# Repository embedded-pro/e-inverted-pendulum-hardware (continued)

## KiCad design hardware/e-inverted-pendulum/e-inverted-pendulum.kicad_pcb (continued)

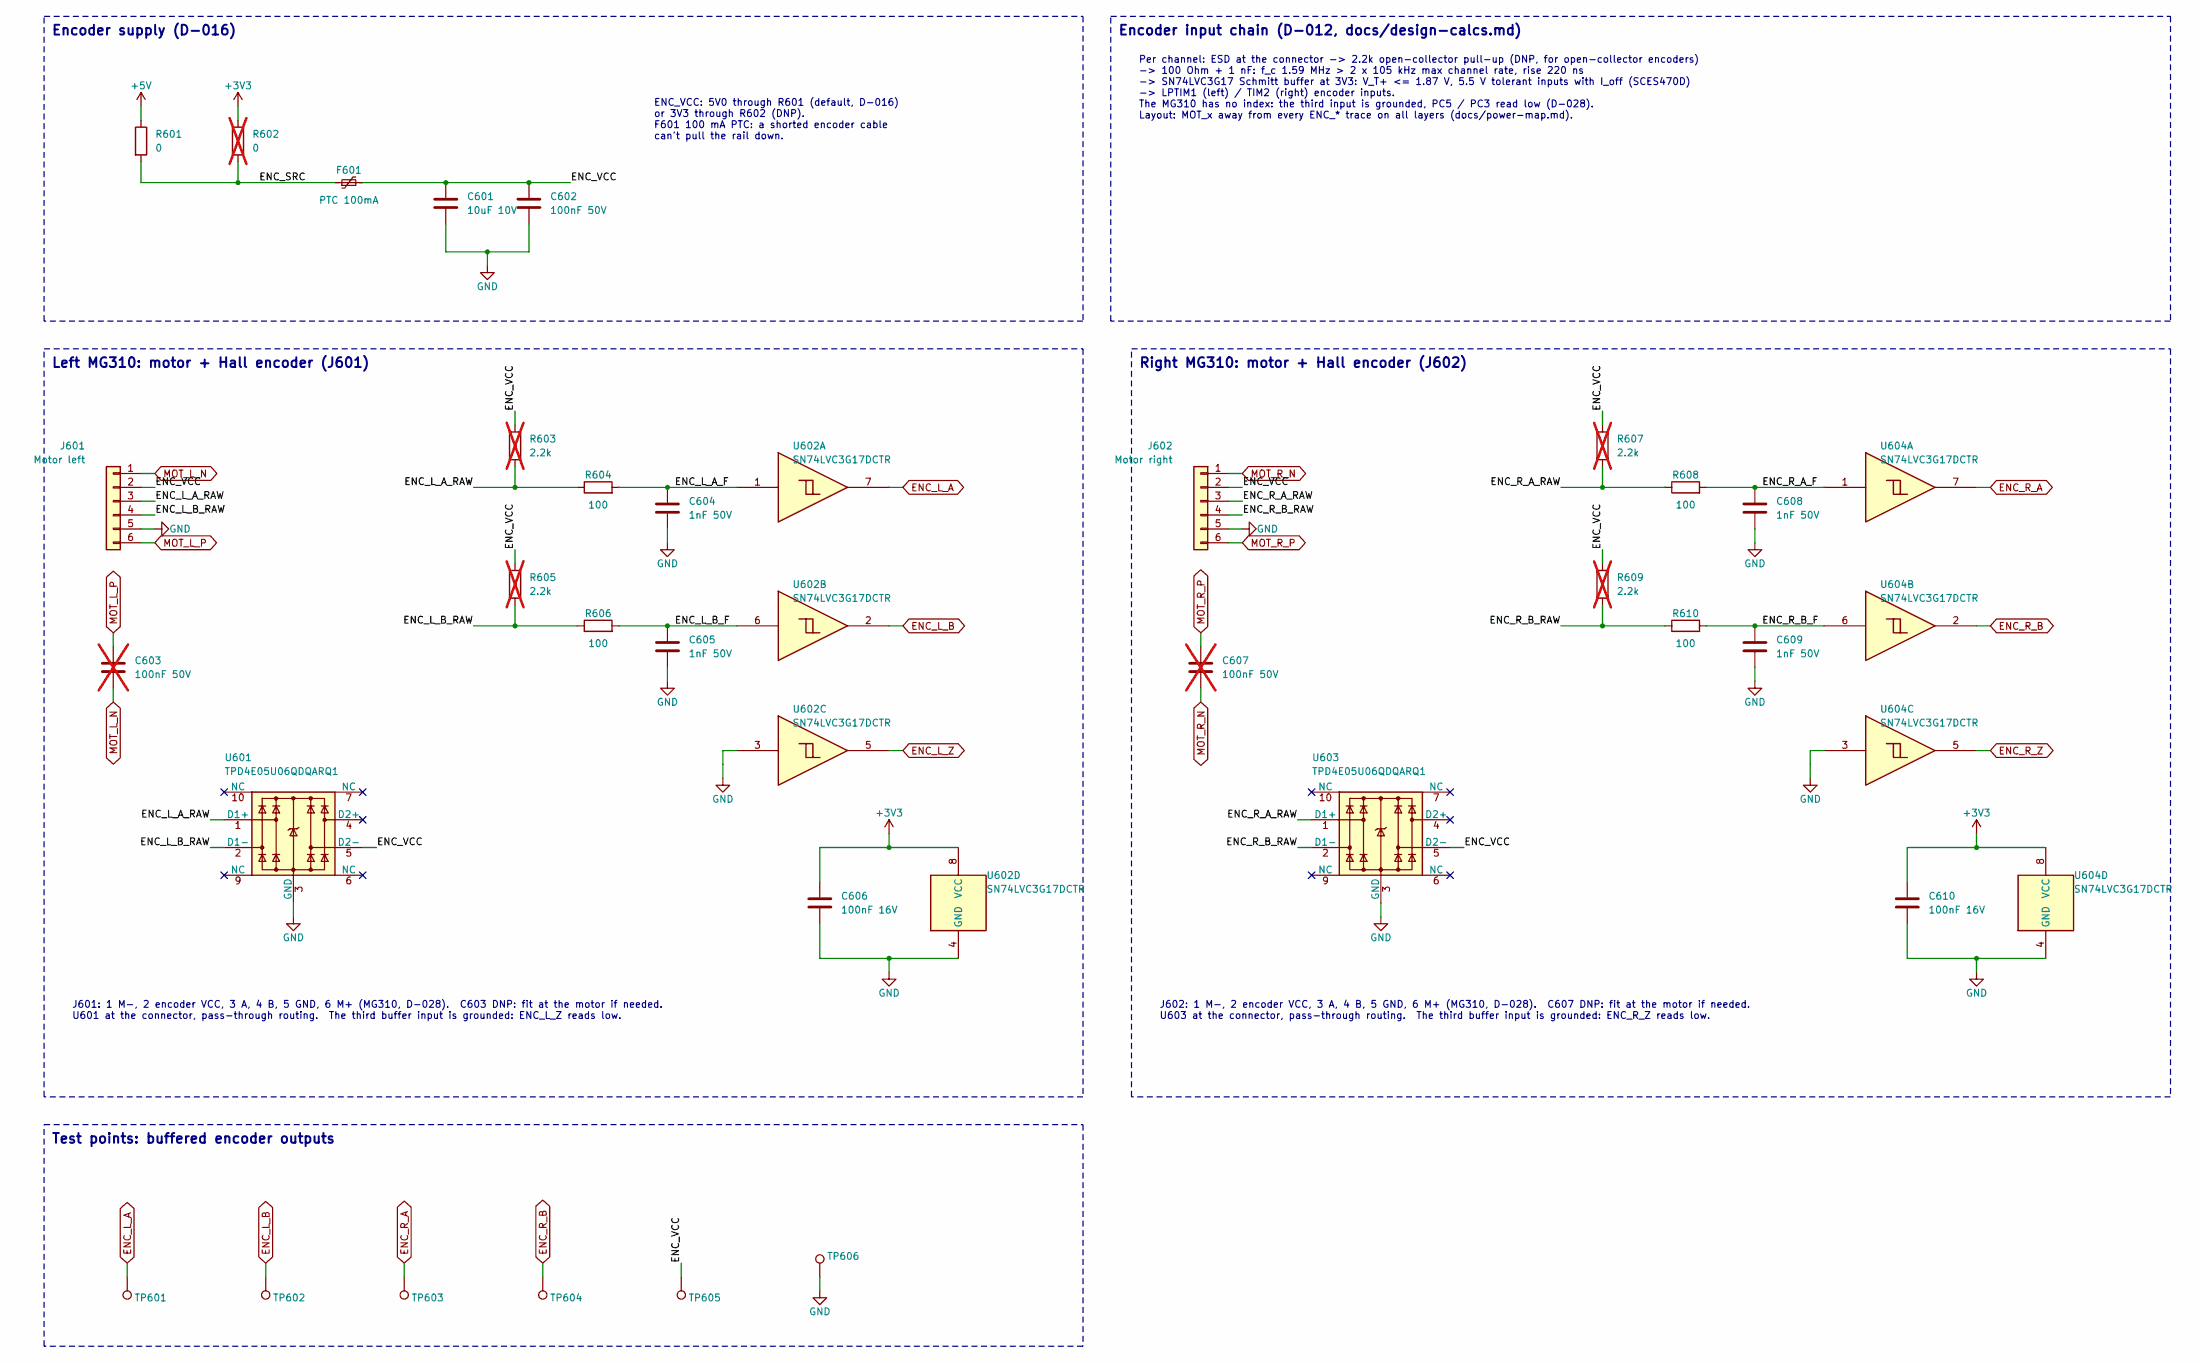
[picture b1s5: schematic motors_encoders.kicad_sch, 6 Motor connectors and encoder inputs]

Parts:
C601: 10uF 10V; C_0603_1608Metric; MPN CL10A106KP8NNNC; LCSC C19702
C602: 100nF 50V; C_0603_1608Metric; MPN CC0603KRX7R9BB104; LCSC C14663
C603, C607: 100nF 50V; C_0603_1608Metric; MPN CC0603KRX7R9BB104; LCSC C14663; not fitted
C604, C605, C608, C609: 1nF 50V; C_0603_1608Metric; MPN CL10B102KB8NNNC; LCSC C1588
C606, C610: 100nF 16V; C_0402_1005Metric; MPN CL05B104KO5NNNC; LCSC C1525
F601: PTC 100mA; Fuse_0805_2012Metric; MPN SMD0805P010TF; LCSC C20975
J601: Motor left; JST_PH_S6B-PH-K_1x06_P2.00mm_Horizontal; MPN S6B-PH-K-S(LF)(SN); LCSC C157920
J602: Motor right; JST_PH_S6B-PH-K_1x06_P2.00mm_Horizontal; MPN S6B-PH-K-S(LF)(SN); LCSC C157920
R601: 0; R_0603_1608Metric; MPN 0603WAF0000T5E; LCSC C21189
R602: 0; R_0603_1608Metric; MPN 0603WAF0000T5E; LCSC C21189; not fitted
R603, R605, R607, R609: 2.2k; R_0603_1608Metric; MPN 0603WAF2201T5E; LCSC C4190; not fitted
R604, R606, R608, R610: 100; R_0603_1608Metric; MPN 0603WAF1000T5E; LCSC C22775
TP601: ENC_L_A; TestPoint_Pad_D1.0mm
TP602: ENC_L_B; TestPoint_Pad_D1.0mm
TP603: ENC_R_A; TestPoint_Pad_D1.0mm
TP604: ENC_R_B; TestPoint_Pad_D1.0mm
TP605: ENC_VCC; TestPoint_Pad_D1.5mm
TP606: GND; TestPoint_Pad_D1.5mm
U601, U603: TPD4E05U06QDQARQ1; USON-10_2.5x1.0mm_P0.5mm; MPN TPD4E05U06QDQARQ1; LCSC C81353
U602, U604: SN74LVC3G17DCTR; SSOP-8_2.95x2.8mm_P0.65mm; MPN SN74LVC3G17DCTR; LCSC C18213

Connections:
+3V3: C606.1, C610.1, R602.1, U602.8 (VCC), U604.8 (VCC); also elsewhere on the board
+5V: R601.1; also elsewhere on the board
/6 Motor connectors and encoder inputs/ENC_L_A_F: C604.1, R604.2, U602.1
/6 Motor connectors and encoder inputs/ENC_L_A_RAW: J601.3, R603.1, R604.1, U601.1 (D1+)
/6 Motor connectors and encoder inputs/ENC_L_B_F: C605.1, R606.2, U602.6
/6 Motor connectors and encoder inputs/ENC_L_B_RAW: J601.4, R605.1, R606.1, U601.2 (D1-)
/6 Motor connectors and encoder inputs/ENC_R_A_F: C608.1, R608.2, U604.1
/6 Motor connectors and encoder inputs/ENC_R_A_RAW: J602.3, R607.1, R608.1, U603.1 (D1+)
/6 Motor connectors and encoder inputs/ENC_R_B_F: C609.1, R610.2, U604.6
/6 Motor connectors and encoder inputs/ENC_R_B_RAW: J602.4, R609.1, R610.1, U603.2 (D1-)
/6 Motor connectors and encoder inputs/ENC_SRC: F601.1, R601.2, R602.2
/6 Motor connectors and encoder inputs/ENC_VCC: C601.1, C602.1, F601.2, J601.2, J602.2, R603.2, R605.2, R607.2, R609.2, TP605.1, U601.5 (D2-), U603.5 (D2-)
ENC_L_A: TP601.1, U602.7; also elsewhere on the board
ENC_L_B: TP602.1, U602.2; also elsewhere on the board
ENC_L_Z: U602.5; also elsewhere on the board
ENC_R_A: TP603.1, U604.7; also elsewhere on the board
ENC_R_B: TP604.1, U604.2; also elsewhere on the board
ENC_R_Z: U604.5; also elsewhere on the board
GND: C601.2, C602.2, C604.2, C605.2, C606.2, C608.2, C609.2, C610.2, J601.5, J602.5, TP606.1, U601.3 (GND), U601.8 (GND), U602.3, U602.4 (GND), U603.3 (GND), U603.8 (GND), U604.3, U604.4 (GND); also elsewhere on the board
MOT_L_N: C603.2, J601.1; also elsewhere on the board
MOT_L_P: C603.1, J601.6; also elsewhere on the board
MOT_R_N: C607.2, J602.1; also elsewhere on the board
MOT_R_P: C607.1, J602.6; also elsewhere on the board

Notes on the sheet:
Per channel: ESD at the connector -> 2.2k open-collector pull-up (DNP, for open-collector encoders) -> 100 Ohm + 1 nF: f_c 1.59 MHz > 2 x 105 kHz max channel rate, rise 220 ns -> SN74LVC3G17 Schmitt buffer at 3V3: V_T+ <= 1.87 V, 5.5 V tolerant inputs with I_off (SCES470D) -> LPTIM1 (left) / TIM2 (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
Right MG310: motor + Hall encoder (J602)
J602: 1 M-, 2 encoder VCC, 3 A, 4 B, 5 GND, 6 M+ (MG310, D-028). C607 DNP: fit at the motor if needed. U603 at the connector, pass-through routing. The third buffer input is grounded: ENC_R_Z reads low.
J601: 1 M-, 2 encoder VCC, 3 A, 4 B, 5 GND, 6 M+ (MG310, D-028). C603 DNP: fit at the motor if needed. U601 at the connector, pass-through routing. The third buffer input is grounded: ENC_L_Z reads low.
Encoder input chain (D-012, docs/design-calcs.md)
ENC_VCC: 5V0 through R601 (default, D-016) or 3V3 through R602 (DNP). F601 100 mA PTC: a shorted encoder cable can't pull the rail down.
Left MG310: motor + Hall encoder (J601)
Test points: buffered encoder outputs
Encoder supply (D-016)

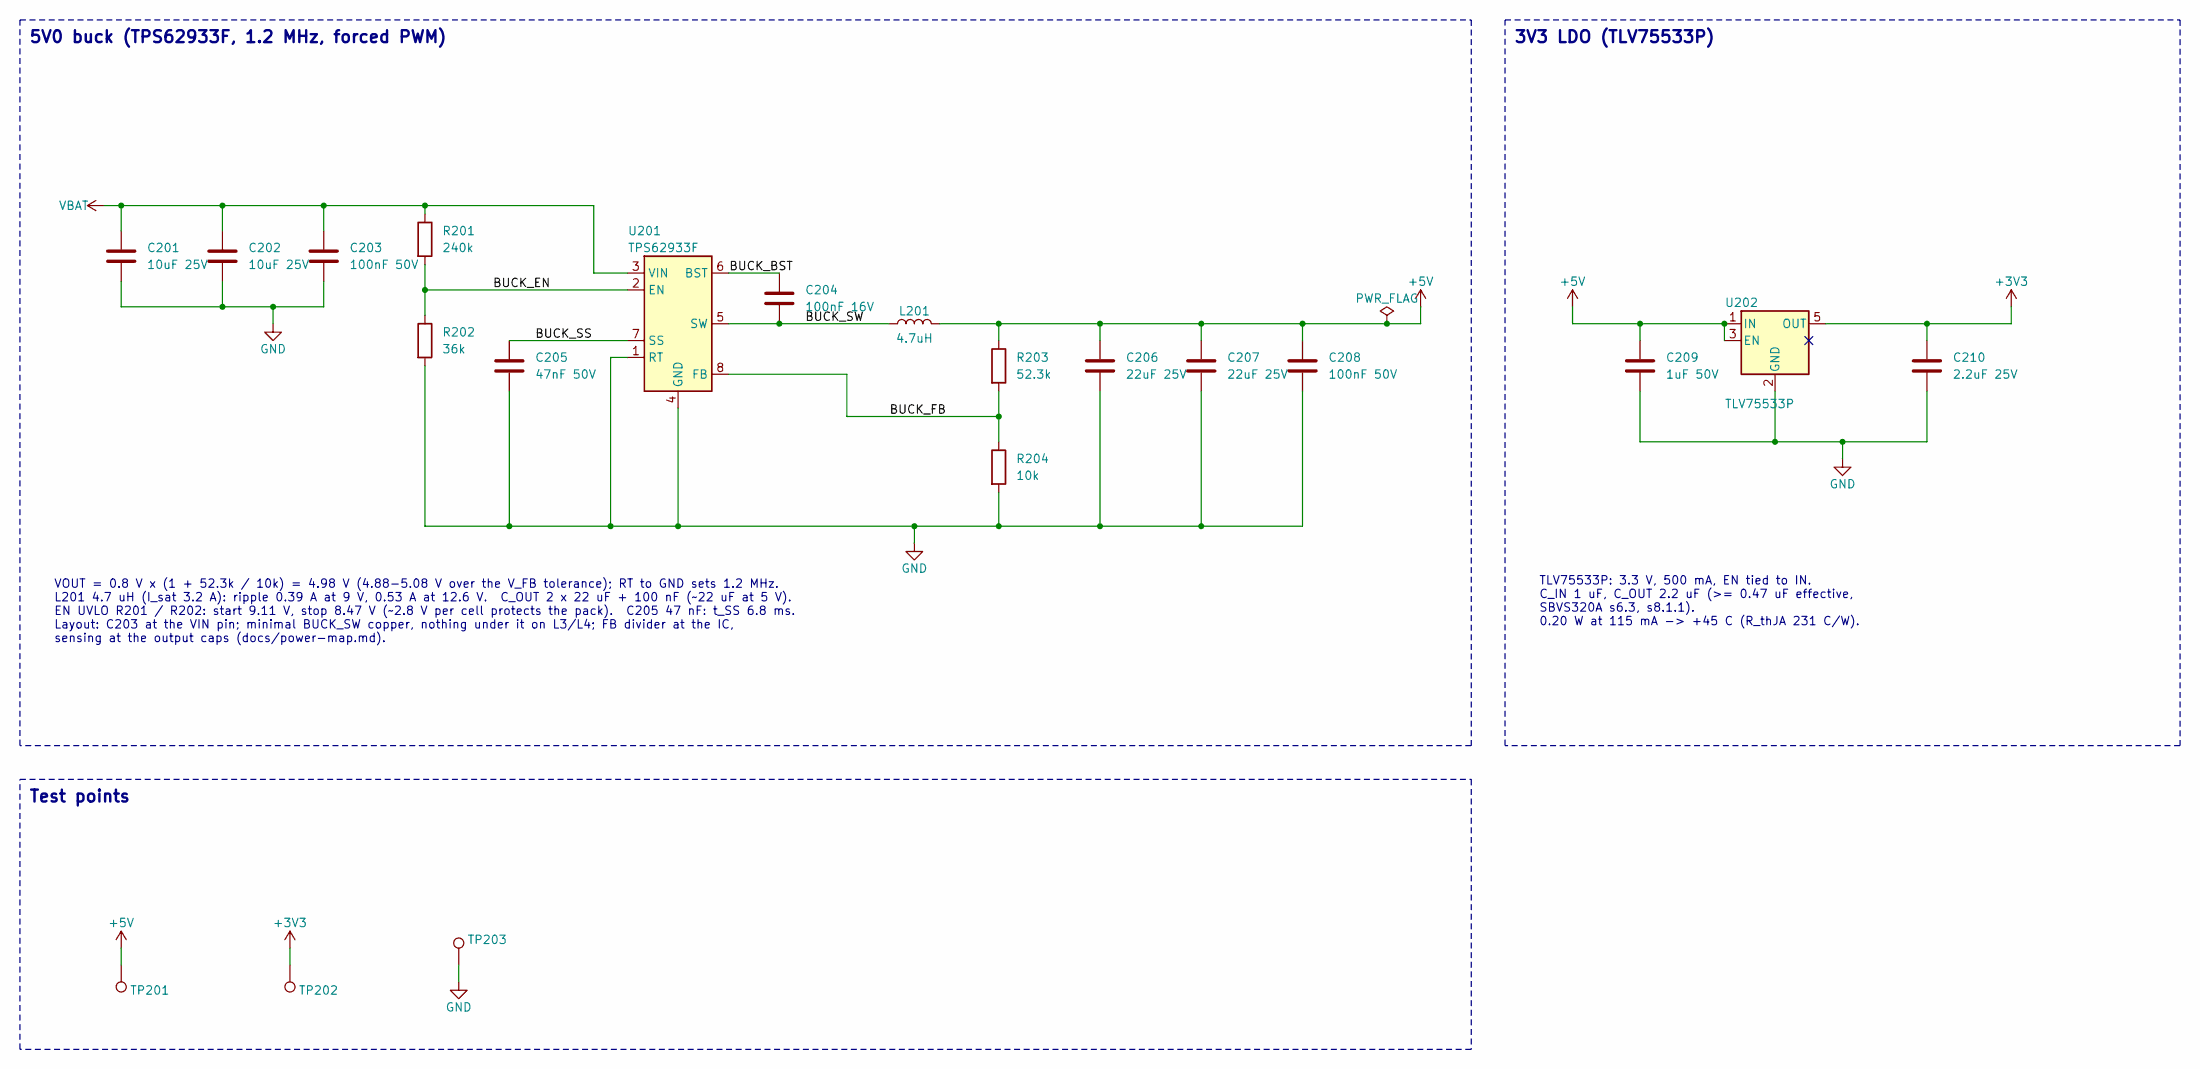
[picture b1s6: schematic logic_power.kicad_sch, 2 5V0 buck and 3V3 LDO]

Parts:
C201, C202: 10uF 25V; C_0805_2012Metric; MPN CL21A106KAYNNNE; LCSC C15850
C203, C208: 100nF 50V; C_0603_1608Metric; MPN CC0603KRX7R9BB104; LCSC C14663
C204: 100nF 16V; C_0402_1005Metric; MPN CL05B104KO5NNNC; LCSC C1525
C205: 47nF 50V; C_0603_1608Metric; MPN CL10B473KB8NNNC; LCSC C1622
C206, C207: 22uF 25V; C_0805_2012Metric; MPN CL21A226MAQNNNE; LCSC C45783
C209: 1uF 50V; C_0603_1608Metric; MPN CL10A105KB8NNNC; LCSC C15849
C210: 2.2uF 25V; C_0603_1608Metric; MPN CL10A225KO8NNNC; LCSC C23630
L201: 4.7uH; L_Sunlord_SWPA4030S; MPN SWPA4030S4R7MT; LCSC C57269
R201: 240k; R_0603_1608Metric; MPN 0603WAF2403T5E; LCSC C4197
R202: 36k; R_0603_1608Metric; MPN 0603WAF3602T5E; LCSC C23147
R203: 52.3k; R_0603_1608Metric; MPN 0603WAF5232T5E; LCSC C23198
R204: 10k; R_0603_1608Metric; MPN 0603WAF1002T5E; LCSC C25804
TP201: +5V; TestPoint_Pad_D1.5mm
TP202: +3V3; TestPoint_Pad_D1.5mm
TP203: GND; TestPoint_Pad_D1.5mm
U201: TPS62933F; SOT-583-8; MPN TPS62933FDRLR; LCSC C5219272
U202: TLV75533P; SOT-23-5; MPN TLV75533PDBVR; LCSC C404027

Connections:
+3V3: C210.1, TP202.1, U202.5 (OUT); also elsewhere on the board
+5V: C206.1, C207.1, C208.1, C209.1, L201.2, R203.1, TP201.1, U202.1 (IN), U202.3 (EN); also elsewhere on the board
/2 5V0 buck and 3V3 LDO/BUCK_BST: C204.1, U201.6 (BST)
/2 5V0 buck and 3V3 LDO/BUCK_EN: R201.2, R202.1, U201.2 (EN)
/2 5V0 buck and 3V3 LDO/BUCK_FB: R203.2, R204.1, U201.8 (FB)
/2 5V0 buck and 3V3 LDO/BUCK_SS: C205.1, U201.7 (SS)
/2 5V0 buck and 3V3 LDO/BUCK_SW: C204.2, L201.1, U201.5 (SW)
GND: C201.2, C202.2, C203.2, C205.2, C206.2, C207.2, C208.2, C209.2, C210.2, R202.2, R204.2, TP203.1, U201.1 (RT), U201.4 (GND), U202.2 (GND); also elsewhere on the board
VBAT: C201.1, C202.1, C203.1, R201.1, U201.3 (VIN); also elsewhere on the board

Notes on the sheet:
VOUT = 0.8 V x (1 + 52.3k / 10k) = 4.98 V (4.88-5.08 V over the V_FB tolerance); RT to GND sets 1.2 MHz. L201 4.7 uH (I_sat 3.2 A): ripple 0.39 A at 9 V, 0.53 A at 12.6 V. C_OUT 2 x 22 uF + 100 nF (~22 uF at 5 V). EN UVLO R201 / R202: start 9.11 V, stop 8.47 V (~2.8 V per cell protects the pack). C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
3V3 LDO (TLV75533P)
TLV75533P: 3.3 V, 500 mA, EN tied to IN. C_IN 1 uF, C_OUT 2.2 uF (>= 0.47 uF effective, SBVS320A s6.3, s8.1.1). 0.20 W at 115 mA -> +45 C (R_thJA 231 C/W).
Test points
5V0 buck (TPS62933F, 1.2 MHz, forced PWM)

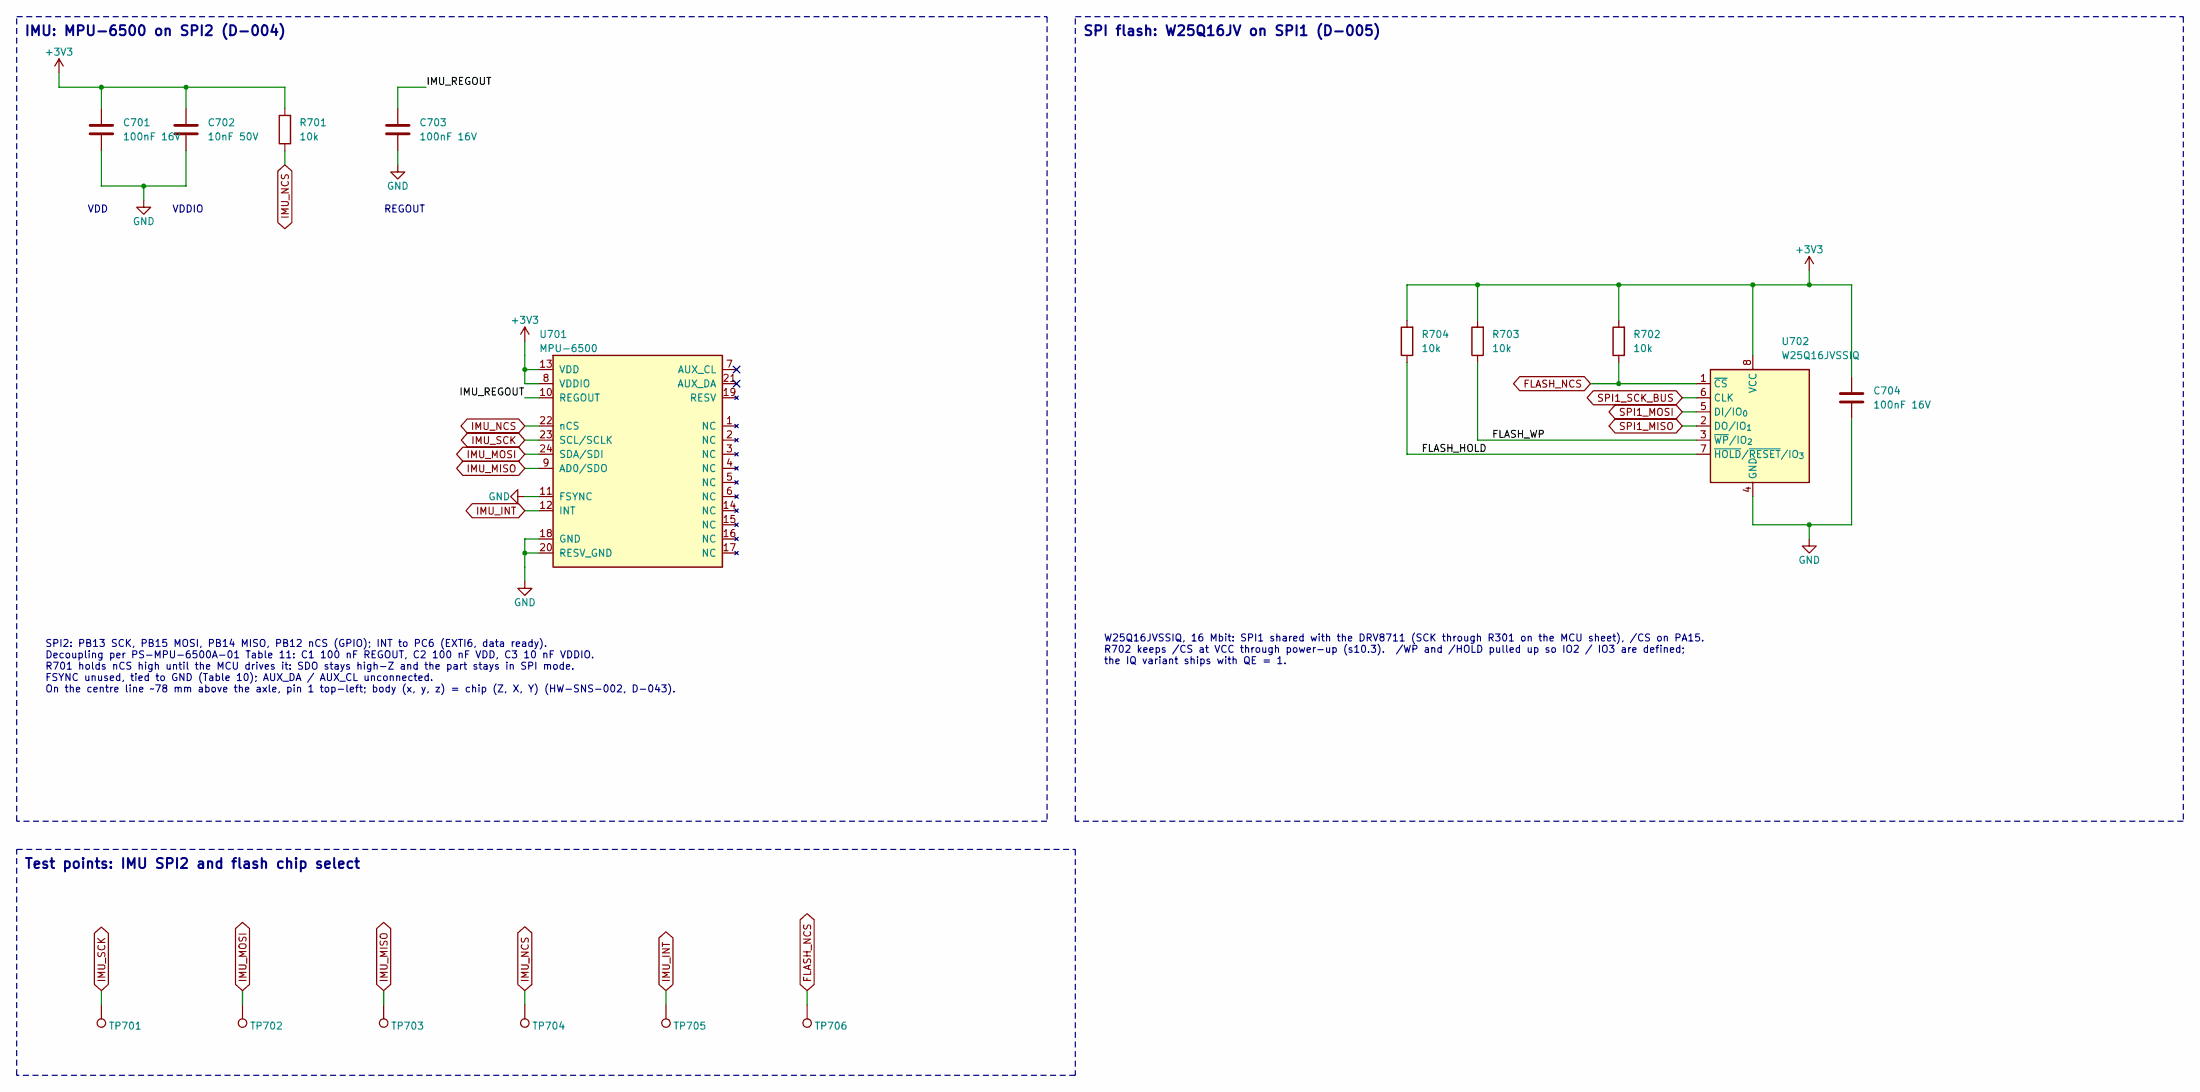
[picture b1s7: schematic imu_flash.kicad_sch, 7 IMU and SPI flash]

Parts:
C701, C703, C704: 100nF 16V; C_0402_1005Metric; MPN CL05B104KO5NNNC; LCSC C1525
C702: 10nF 50V; C_0603_1608Metric; MPN CL10B103KB8NNNC; LCSC C1589
R701, R702, R703, R704: 10k; R_0603_1608Metric; MPN 0603WAF1002T5E; LCSC C25804
TP701: IMU_SCK; TestPoint_Pad_D1.0mm
TP702: IMU_MOSI; TestPoint_Pad_D1.0mm
TP703: IMU_MISO; TestPoint_Pad_D1.0mm
TP704: IMU_NCS; TestPoint_Pad_D1.0mm
TP705: IMU_INT; TestPoint_Pad_D1.0mm
TP706: FLASH_NCS; TestPoint_Pad_D1.0mm
U701: MPU-6500; InvenSense_QFN-24_3x3mm_P0.4mm; MPN MPU-6500; LCSC C50278
U702: W25Q16JVSSIQ; SOIC-8_5.3x5.3mm_P1.27mm; MPN W25Q16JVSSIQ; LCSC C131025

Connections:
+3V3: C701.1, C702.1, C704.1, R701.2, R702.2, R703.2, R704.2, U701.8 (VDDIO), U701.13 (VDD), U702.8 (VCC); also elsewhere on the board
/7 IMU and SPI flash/FLASH_HOLD: R704.1, U702.7 (~HOLD/~RESET/IO_{3})
/7 IMU and SPI flash/FLASH_WP: R703.1, U702.3 (~WP/IO_{2})
/7 IMU and SPI flash/IMU_REGOUT: C703.1, U701.10 (REGOUT)
FLASH_NCS: R702.1, TP706.1, U702.1 (~CS); also elsewhere on the board
GND: C701.2, C702.2, C703.2, C704.2, U701.11 (FSYNC), U701.18 (GND), U701.20 (RESV_GND), U702.4 (GND); also elsewhere on the board
IMU_INT: TP705.1, U701.12 (INT); also elsewhere on the board
IMU_MISO: TP703.1, U701.9 (AD0/SDO); also elsewhere on the board
IMU_MOSI: TP702.1, U701.24 (SDA/SDI); also elsewhere on the board
IMU_NCS: R701.1, TP704.1, U701.22 (nCS); also elsewhere on the board
IMU_SCK: TP701.1, U701.23 (SCL/SCLK); also elsewhere on the board
SPI1_MISO: U702.2 (DO/IO_{1}); also elsewhere on the board
SPI1_MOSI: U702.5 (DI/IO_{0}); also elsewhere on the board
SPI1_SCK_BUS: U702.6 (CLK); also elsewhere on the board

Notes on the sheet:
VDD
SPI flash: W25Q16JV on SPI1 (D-005)
W25Q16JVSSIQ, 16 Mbit: SPI1 shared with the DRV8711 (SCK through R301 on the MCU sheet), /CS on PA15. R702 keeps /CS at VCC through power-up (s10.3). /WP and /HOLD pulled up so IO2 / IO3 are defined; the IQ variant ships with QE = 1.
REGOUT
SPI2: PB13 SCK, PB15 MOSI, PB14 MISO, PB12 nCS (GPIO); INT to PC6 (EXTI6, data ready). Decoupling per PS-MPU-6500A-01 Table 11: C1 100 nF REGOUT, C2 100 nF VDD, C3 10 nF VDDIO. R701 holds nCS high until the MCU drives it: SDO stays high-Z and the part stays in SPI mode. FSYNC unused, tied to GND (T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
Test points: IMU SPI2 and flash chip select
VDDIO
IMU: MPU-6500 on SPI2 (D-004)

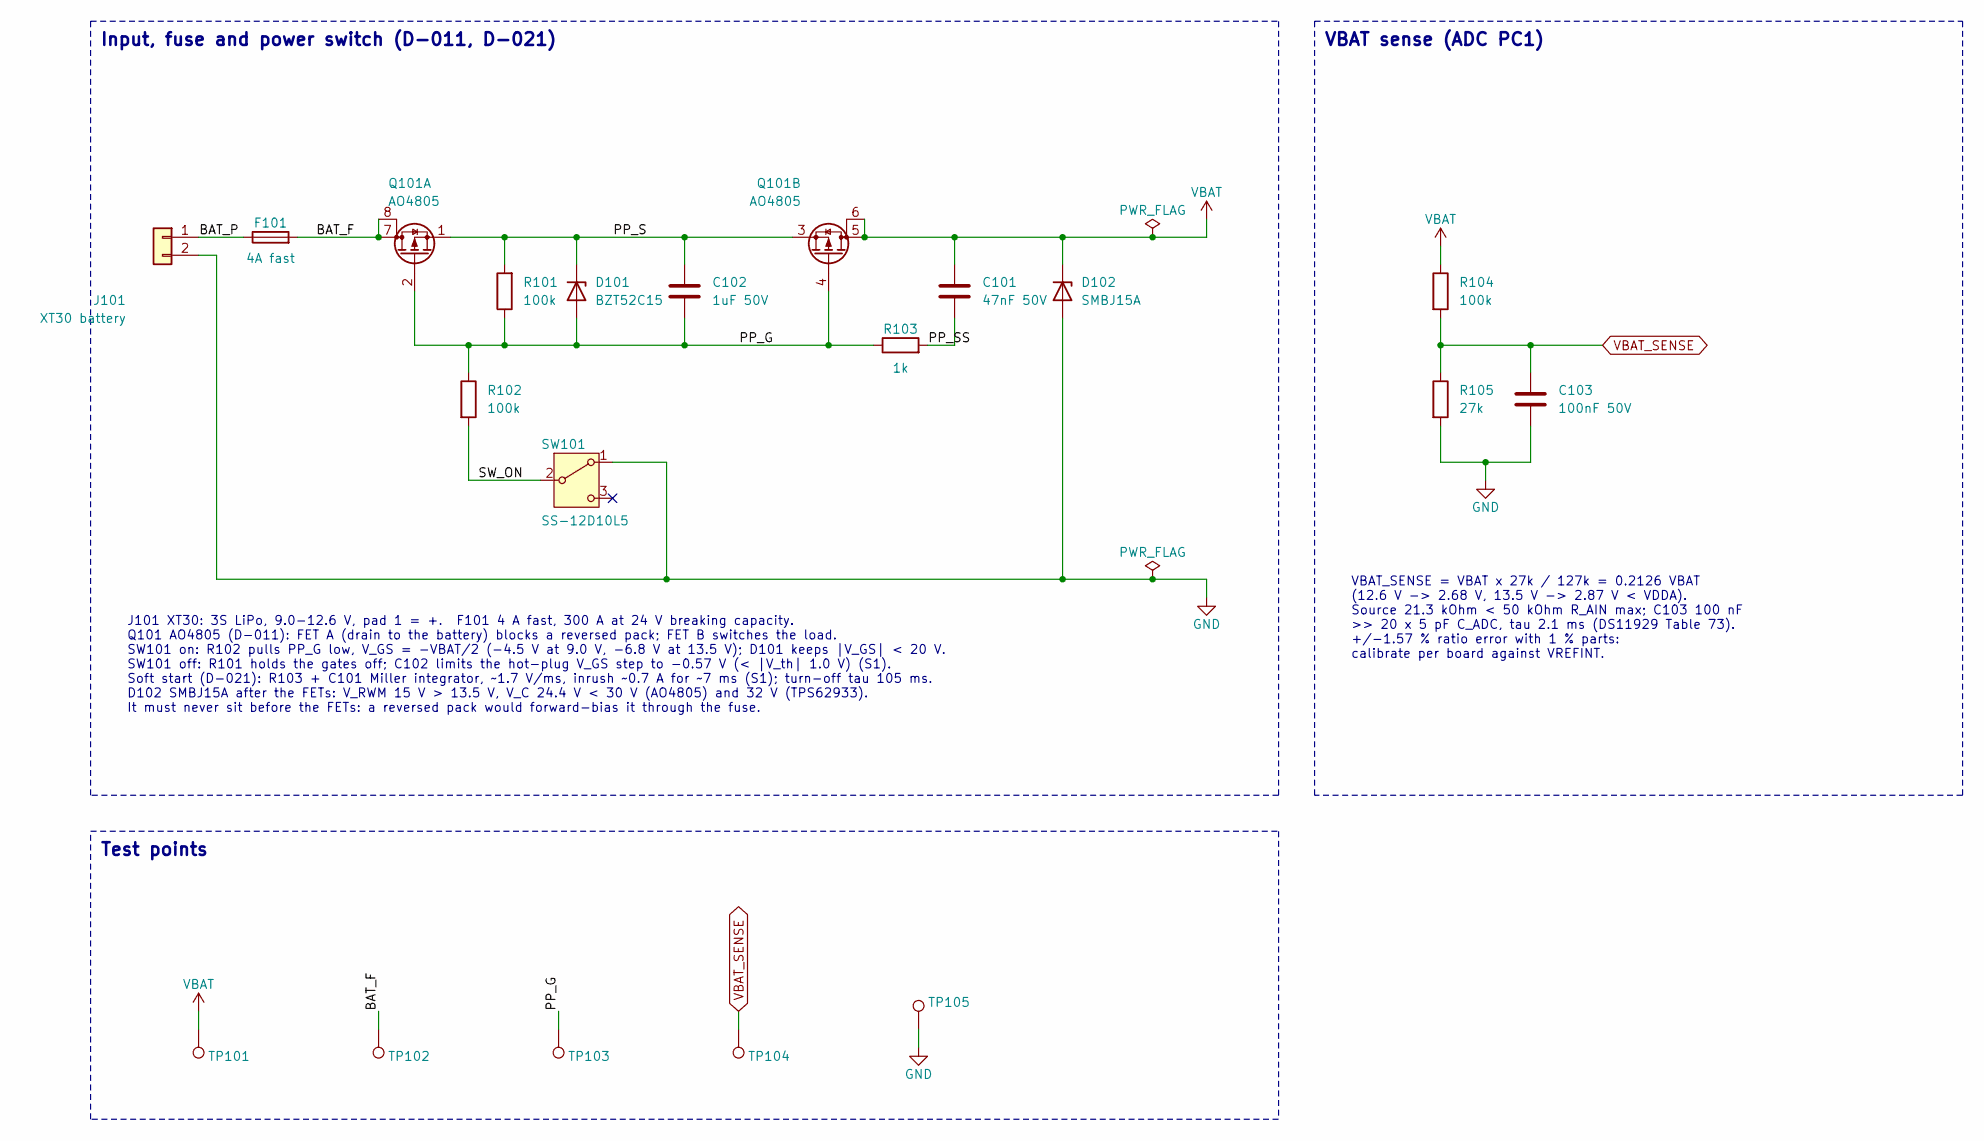
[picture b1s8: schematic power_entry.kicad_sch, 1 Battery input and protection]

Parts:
C101: 47nF 50V; C_0603_1608Metric; MPN CL10B473KB8NNNC; LCSC C1622
C102: 1uF 50V; C_0603_1608Metric; MPN CL10A105KB8NNNC; LCSC C15849
C103: 100nF 50V; C_0603_1608Metric; MPN CC0603KRX7R9BB104; LCSC C14663
D101: BZT52C15; D_SOD-123; MPN BZT52C15; LCSC C2104
D102: SMBJ15A; D_SMB; MPN SMBJ15A; LCSC C83846
F101: 4A fast; Fuse_1206_3216Metric; MPN 1206FA-4A; LCSC C2937379
J101: XT30 battery; AMASS_XT30UPB-F_1x02_P5.00mm_Vertical; MPN XT30UPB-F30.G.Y; LCSC C108769
Q101: AO4805; SOIC-8_3.9x4.9mm_P1.27mm; MPN AO4805; LCSC C3040596
R101, R102, R104: 100k; R_0603_1608Metric; MPN 0603WAF1003T5E; LCSC C25803
R103: 1k; R_0603_1608Metric; MPN 0603WAF1001T5E; LCSC C21190
R105: 27k; R_0603_1608Metric; MPN 0603WAF2702T5E; LCSC C22967
SW101: SS-12D10L5; SW_Slide_SPDT_SS-12D10L5_P4.70mm; MPN SS-12D10L5; LCSC C319012
TP101: VBAT; TestPoint_Pad_D1.5mm
TP102: BAT_F; TestPoint_Pad_D1.0mm
TP103: PP_G; TestPoint_Pad_D1.0mm
TP104: VBAT_SENSE; TestPoint_Pad_D1.0mm
TP105: GND; TestPoint_Pad_D1.5mm

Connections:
/1 Battery input and protection/BAT_F: F101.2, Q101.7 (D), Q101.8 (D), TP102.1
/1 Battery input and protection/BAT_P: F101.1, J101.1
/1 Battery input and protection/PP_G: C102.1, D101.2 (A), Q101.2 (G), Q101.4 (G), R101.1, R102.1, R103.1, TP103.1
/1 Battery input and protection/PP_S: C102.2, D101.1 (K), Q101.1 (S), Q101.3 (S), R101.2
/1 Battery input and protection/PP_SS: C101.1, R103.2
/1 Battery input and protection/SW_ON: R102.2, SW101.2 (B)
GND: C103.2, D102.2 (A), J101.2, R105.2, SW101.1 (A), TP105.1; also elsewhere on the board
VBAT: C101.2, D102.1 (K), Q101.5 (D), Q101.6 (D), R104.1, TP101.1; also elsewhere on the board
VBAT_SENSE: C103.1, R104.2, R105.1, TP104.1; also elsewhere on the board

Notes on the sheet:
J101 XT30: 3S LiPo, 9.0-12.6 V, pad 1 = +. F101 4 A fast, 300 A at 24 V breaking capacity. Q101 AO4805 (D-011): FET A (drain to the battery) blocks a reversed pack; FET B switches the load. SW101 on: R102 pulls PP_G low, V_GS = -VBAT/2 (-4.5 V at 9.0 V, -6.8 V at 13.5 V); D101 keeps |V_GS| < 20 V. 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
Input, fuse and power switch (D-011, D-021)
VBAT sense (ADC PC1)
VBAT_SENSE = VBAT x 27k / 127k = 0.2126 VBAT (12.6 V -> 2.68 V, 13.5 V -> 2.87 V < VDDA). Source 21.3 kOhm < 50 kOhm R_AIN max; C103 100 nF >> 20 x 5 pF C_ADC, tau 2.1 ms (DS11929 Table 73). +/-1.57 % ratio error with 1 % parts: calibrate per board against VREFINT.
Test points

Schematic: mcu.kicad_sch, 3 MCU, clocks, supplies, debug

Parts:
C301, C302, C303, C304, C305, C312, C317: 100nF 16V; C_0402_1005Metric; MPN CL05B104KO5NNNC; LCSC C1525
C306: 4.7uF 10V; C_0402_1005Metric; MPN CL05A475MP5NRNC; LCSC C23733
C307, C318: 100nF 16V; MB1355_0402_CAP_NPOL; MPN CL05B104KO5NNNC; LCSC C1525
C308: 100pF 50V; MB1355_0402_CAP_NPOL; MPN CL05C101JB5NNNC; LCSC C26409
C309, C314: 4.7uF 10V; MB1355_0402_CAP_NPOL; MPN CL05A475MP5NRNC; LCSC C23733
C310: 10nF 50V; C_0603_1608Metric; MPN CL10B103KB8NNNC; LCSC C1589
C311, C313: 1uF 50V; C_0603_1608Metric; MPN CL10A105KB8NNNC; LCSC C15849
C315, C316: 6.8pF 50V; MB1355_0402_CAP_NPOL; MPN CL05C6R8CB5NNNC; LCSC C318598
FB301: BLM18PG221SN1D; L_0603_1608Metric; MPN BLM18PG221SN1D; LCSC C80165
J301: STDC14; PinHeader_2x07_P1.27mm_Vertical_SMD; MPN FTSH-107-01-L-DV-K; LCSC C5307809
L301: 10uH; MB1355_0805_COIL; MPN LQM21FN100M80L; LCSC C162582
L302: 10nH; MB1355_IND_0402_MURATA_LQW15AN_H0P5; MPN LQG15HS10NJ02D; LCSC C77103
R301: 33; R_0603_1608Metric; MPN 0603WAF330JT5E; LCSC C23140
R302: 10k; R_0603_1608Metric; MPN 0603WAF1002T5E; LCSC C25804
TP301: NRST; TestPoint_Pad_D1.0mm
TP302: BOOT0; TestPoint_Pad_D1.0mm
TP303: VDDA; TestPoint_Pad_D1.5mm
TP304: VFBSMPS; TestPoint_Pad_D1.0mm
U301: STM32WB55RGV6; QFN-68-1EP_8x8mm_P0.4mm_EP6.4x6.4mm; MPN STM32WB55RGV6; LCSC C401505
Y301: 32MHz; MB1355_NX2016_4P; MPN NX2016SA-32MHZ-EXS00A-CS06654; LCSC C5441424
Y302: 32.768kHz; MB1355_NX2012_2P; MPN NX2012SA-32.768KHZ-STD-MUB-3; LCSC C889705

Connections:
+3V3: C301.1, C302.1, C303.1, C304.1, C305.1, C306.1, C307.1, C308.1, C309.1, C318.1, FB301.1, J301.3 (VCC), U301.1 (VBAT), U301.30 (VDD), U301.33 (VDDRF), U301.44 (VDDSMPS), U301.45 (VDD), U301.55 (VDDUSB), U301.68 (VDD); also elsewhere on the board
/3 MCU, clocks, supplies, debug/BOOT0: R302.1, TP302.1, U301.5 (PH3)
/3 MCU, clocks, supplies, debug/HSE_IN: U301.35 (OSC_IN), Y301.1
/3 MCU, clocks, supplies, debug/HSE_OUT: U301.34 (OSC_OUT), Y301.3
/3 MCU, clocks, supplies, debug/NRST: C317.1, J301.12 (~RST), TP301.1, U301.8 (NRST)
/3 MCU, clocks, supplies, debug/OSC32_IN: C315.1, U301.3 (PC14), Y302.1
/3 MCU, clocks, supplies, debug/OSC32_OUT: C316.1, U301.4 (PC15), Y302.2
/3 MCU, clocks, supplies, debug/SMPS_LX: L302.1, U301.43 (VLXSMPS)
/3 MCU, clocks, supplies, debug/SMPS_MID: L301.1, L302.2
/3 MCU, clocks, supplies, debug/SPI1_SCK: R301.1, U301.63 (PB3)
/3 MCU, clocks, supplies, debug/SWCLK: J301.6 (JCLK/SWCLK), U301.56 (PA14)
/3 MCU, clocks, supplies, debug/SWDIO: J301.4 (JTMS/SWDIO), U301.54 (PA13)
/3 MCU, clocks, supplies, debug/VCP_RX: J301.13 (VCP_RX), U301.67 (PB7)
/3 MCU, clocks, supplies, debug/VCP_TX: J301.14 (VCP_TX), U301.66 (PB6)
/3 MCU, clocks, supplies, debug/VFBSMPS: C314.1, L301.2, TP304.1, U301.41 (VFBSMPS)
DRV_AIN1: U301.51 (PA10); also elsewhere on the board
DRV_AIN2: U301.52 (PA11); also elsewhere on the board
DRV_BIN1: U301.23 (PA8); also elsewhere on the board
DRV_BIN2: U301.24 (PA9); also elsewhere on the board
DRV_NFAULT: U301.21 (PA6), U301.25 (PC4); also elsewhere on the board
DRV_NSLEEP: U301.6 (PB8); also elsewhere on the board
DRV_NSTALL: U301.27 (PB2); also elsewhere on the board
DRV_RESET: U301.7 (PB9); also elsewhere on the board
DRV_SCS: U301.19 (PA4); also elsewhere on the board
ENC_L_A: U301.9 (PC0); also elsewhere on the board
ENC_L_B: U301.11 (PC2); also elsewhere on the board
ENC_L_Z: U301.26 (PC5); also elsewhere on the board
ENC_R_A: U301.15 (PA0); also elsewhere on the board
ENC_R_B: U301.16 (PA1); also elsewhere on the board
ENC_R_Z: U301.12 (PC3); also elsewhere on the board
FLASH_NCS: U301.57 (PA15); also elsewhere on the board
GND: C301.2, C302.2, C303.2, C304.2, C305.2, C306.2, C307.2, C308.2, C309.2, C310.2, C311.2, C312.2, C313.2, C314.2, C315.2, C316.2, C317.2, C318.2, J301.5 (GND), J301.7 (GND), J301.11 (GNDDetect), R302.2, U301.32 (VSSRF), U301.42 (VSSSMPS), U301.69 (VSS), Y301.2 (G), Y301.4 (G); also elsewhere on the board
IMU_INT: U301.50 (PC6); also elsewhere on the board
IMU_MISO: U301.48 (PB14); also elsewhere on the board
IMU_MOSI: U301.49 (PB15); also elsewhere on the board
IMU_NCS: U301.46 (PB12); also elsewhere on the board
IMU_SCK: U301.47 (PB13); also elsewhere on the board
LED_DATA: U301.22 (PA7); also elsewhere on the board
LED_GREEN: U301.38 (PB0); also elsewhere on the board
NFC_GPO: U301.17 (PA2); also elsewhere on the board
NFC_RF_DIS: U301.18 (PA3); also elsewhere on the board
QWIIC_SCL: U301.28 (PB10); also elsewhere on the board
QWIIC_SDA: U301.29 (PB11); also elsewhere on the board
RF1: U301.31 (RF1); also elsewhere on the board
SPI1_MISO: U301.64 (PB4); also elsewhere on the board
SPI1_MOSI: U301.65 (PB5); also elsewhere on the board
SPI1_SCK_BUS: R301.2; also elsewhere on the board
VBAT_SENSE: U301.10 (PC1); also elsewhere on the board
VDDA: C310.1, C311.1, C312.1, C313.1, FB301.2, TP303.1, U301.13 (VREF+), U301.14 (VDDA)

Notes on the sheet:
PC5 PA0 PA1 PC3 PB6 PB7 PB0 PA13 PA14 PA15 PC1 PA7 PB10 PB11 PB2 PH3 PA2 PA3
VDDRF 33
One 100 nF per supply pin, at the pin, each with its own via; 4.7 uF bulk on VDD. VDDRF 100 nF + 100 pF at pin 33, VDDSMPS 4.7 uF + 100 nF at pin 44: values and land patterns from MB1355 D-01 (C33 / C34 / C23 / C24, D-037). VDDA and VREF+ through FB301: 10 nF + 1 uF on VDDA, 100 nF + 1 uF on VREF+ 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
VDDSMPS 44
VDD 30
VDD 45
PA8 PA9 PA10 PA11 PA6 PC4 PB3 PB4 PB5 PA4 PB8 PB9 PB13 PB14 PB15 PB12 PC6 PC0 PC2
VDDA 14
Debug and virtual COM port: STDC14 (D-009)
VDDUSB 55
VREF+ 13
VBAT 1
ENC_L_Z ENC_R_A ENC_R_B ENC_R_Z VCP_TX VCP_RX LED_GREEN SWDIO SWCLK FLASH_NCS VBAT_SENSE LED_DATA QWIIC_SCL QWIIC_SDA DRV_NSTALL BOOT0 NFC_GPO NFC_RF_DIS
DRV_BIN1 DRV_BIN2 DRV_AIN1 DRV_AIN2 DRV_NFAULT DRV_NFAULT SPI1_SCK SPI1_MISO SPI1_MOSI DRV_SCS DRV_NSLEEP DRV_RESET IMU_SCK IMU_MISO IMU_MOSI IMU_NCS IMU_INT ENC_L_A ENC_L_B
VDD bulk
Core SMPS (DS11929 Table 6)
Test points
TIM1_CH1 TIM1_CH2 TIM1_CH3 TIM1_CH4 TIM1_BKIN EXTI4 SPI1_SCK SPI1_MISO SPI1_MOSI GPIO GPIO GPIO SPI2_SCK SPI2_MISO SPI2_MOSI GPIO EXTI6 LPTIM1_IN1 LPTIM1_IN2
Pin plan (pin-data/pinmap.csv, checked by scripts/check_pinmap.py)
Reset, boot and SPI1 clock termination
Clocks: HSE 32 MHz, LSE 32.768 kHz
NRST: 100 nF at the pin (DS11929 Fig. 24); the STDC14 probe drives it too. BOOT0 (PH3): 10k pull-down, no button (D-035): TP302 to +3V3 at reset, or the boot option bytes over SWD. R301 33 Ohm at PB3: source termination of the SCK shared by the DRV8711 and the flash (s9).
STM32WB55RGV6 (UFQFPN-68)
Supplies and decoupling (DS11929 Fig. 16)
STLINK-V3 STDC14 (1.27 mm): SWD + virtual COM port on USART1 (PB6 TX, PB7 RX). SWO (pin 8) unused: PB3 is SPI1_SCK. Pin 3 is the target VCC reference for the probe.
As on MB1355 D-01 (D-037): VLXSMPS -> L302 10 nH -> L301 10 uH -> VFBSMPS, C314 4.7 uF (DS11929 Table 6). ST's land patterns and copper; in-stock equivalents on ST's pads (ST: LQP15MN10NG02, 74479777310A).
HSE NX2016SA (as MB1355 X1): no external caps, load trimmed by HSETUNE (DS11929 Table 5 note 1). LSE NX2012SA MUB-3 C_L 6 pF on MB1355's X2 land: 2 x 6.8 pF C0G (AN2867); ST fits a C_L 7 pF part + 2 x 10 pF.
VDD 68
EXTI5 TIM2_CH1 TIM2_CH2 EXTI3 USART1_TX USART1_RX GPIO SYS_JTMS-SWDIO SYS_JTCK-SWCLK GPIO ADC1_IN2 TIM17_CH1 I2C3_SCL I2C3_SDA GPIO BOOT0 EXTI2 GPIO
